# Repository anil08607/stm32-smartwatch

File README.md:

# Anil nRF52810 Smartwatch V1

A 46 × 46 mm, four-layer Bluetooth smartwatch PCB with a Nordic nRF52810-QFAA, 240 × 240 SPI LCD interface, BMA456 accelerometer, battery-backed PCF8563 RTC, USB-C 5 V charging, protected single-cell battery interface, bonded battery NTC, two buttons and haptic motor output. USB-C faces the left side, clear of both straps; two buttons form a centred pair on the right side.

**Release status: engineering review / prototype handoff. Production ordering is blocked until the explicit gates in `release/readiness.json` are closed.** Passing software checks does not establish RF performance, battery safety, assembly orientation or enclosure fit. No hardware test results or working smartwatch firmware are claimed.

## Open the design

- `index.circuit.tsx`: complete compact product assembly by default, with the actual routed PCB underneath.
- `pcb.circuit.tsx`: dedicated routed PCB/schematic view and PCB-only inspection.
- `assembly-exploded.circuit.tsx`: separated product stack for battery, display, buttons, wiring and enclosure inspection.
- `assembly.circuit.tsx`: routed PCB plus external product assembly in the tscircuit 3D viewer.
- `SMARTWATCH_V1_NRF52810.circuit.tsx`: editable electrical design, exact parts, placement and protected critical routes.
- `hardware/smartwatch-nrf52810.kicad_pro`: portable native KiCad 10 project, seven electrical sheets and local symbol/footprint libraries.
- `mechanical/index.html`: interactive compact/exploded assembly. Run `bun run preview:assembly`, then open http://127.0.0.1:8766/mechanical/.
- `mechanical/`: compact/exploded GLB, five printable STL parts and dimension/part manifest. The provisional case is 54 × 54 × 18 mm with 22 mm strap lugs. Bodies and harnesses are fit envelopes.
- `release/full-purchase-list.csv`: fitted SMT parts, LCD, battery, NTC, motor, harnesses, enclosure, lens, fastening, strap and tools, with purchase URLs.

## Reproduce the checks

Install Bun 1.3.14, then `bun install --frozen-lockfile`. Run `bun run verify` for formatting, type checks, a fresh editable-source build, strict saved-route binding, connectivity, routing, assembly, schematic-style checks, all four actual viewer entries and the hosted multi-file CLI build and a stale-geometry rejection test. `bun run check:native` runs the actual KiCad DRC and ERC (KiCad 10 required; set `KICAD_CLI` if it is not on PATH). `bun run check:stock` refreshes public exact-part JLCPCB inventory. `bun run check:order` is intentionally strict and fails while any qualification or purchasing gate is unresolved.

The hosted build uses `bun run build:site` and only the four public entrypoints. Its optional parts engine is off because footprints and exact MPNs are committed and audited separately; inventory is checked by `check:stock`. No DRC or warning-ignore flags are used. Connector pin-1 display annotations cannot invalidate routing; changes to pads, positions, nets or copper still do.

Source/geometry edits invalidate the routed artifact and release evidence. Follow `routing/README.md`; never bypass the fingerprint or regenerate only the screenshots. Manufacturing outputs come from the reviewed native board, not from an unrouted viewer export.

## Hardware boundaries

The nRF52810 has 192 KiB flash and 24 KiB RAM. A 240 × 240 RGB565 framebuffer needs 115,200 bytes; firmware must use line/tile rendering. This revision has BLE, a no-touch LCD, motion sensing, RTC, buttons and haptics. It does not include Wi-Fi, a touch controller or an optical heart-rate sensor.

The main rail is nominally 3.05 V (510 kΩ / 100 kΩ feedback). The MCU uses its internal LDO; DCC is unconnected and firmware must leave DCDCEN=0. RF matching values are reference starting values. The antenna keepout spans all copper layers; final fabricator stackup, impedance and enclosure tuning remain mandatory.

Only the 70 fitted top-side parts belong in the SMT BOM/CPL. M1 is a pair of motor wire pads with no paste; the motor is installed after reflow. J2 and J5 use identical connector families but carry battery power and NTC respectively: label harnesses and verify polarity before connection.

See [assembly](docs/assembly.md), [fabrication](docs/fabrication.md), [bring-up](docs/bring-up.md), [sourcing](sourcing/README.md), [firmware interface](firmware/README.md) and [manufacturer references](REFERENCES.md).

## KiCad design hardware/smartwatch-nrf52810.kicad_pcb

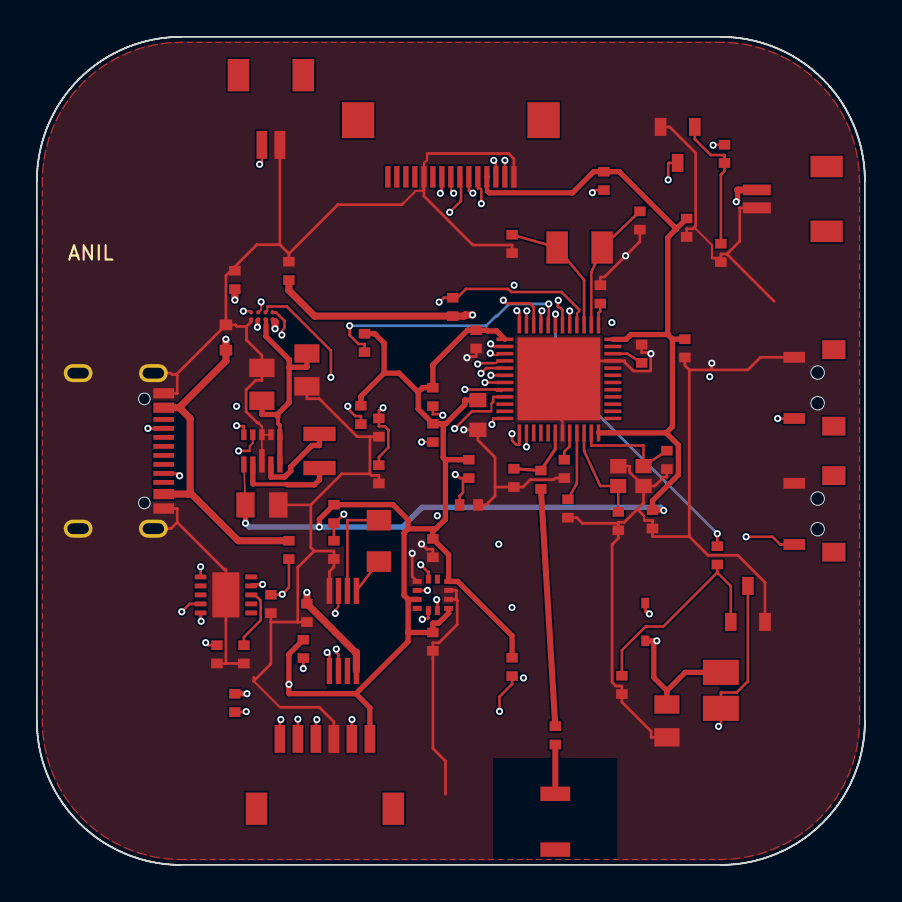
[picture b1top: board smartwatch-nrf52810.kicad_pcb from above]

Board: 4 copper layers, 46.0 x 46.0 mm, 71 parts (0 on the bottom side), 53 nets.

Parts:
ANT1: RFANT3216120A5T; ANT1_exact
C1: 1uF; C1_exact
C2: 10uF; C2_exact
C3: 1uF; C3_exact
C4: 10uF; C4_exact
C5: 22uF; C5_exact
C6: 1uF; C6_exact
C8: 100nF; C8_exact
C9: 100pF; C9_exact
C10: 100nF; C10_exact
C11: 1uF; C11_exact
C12: 4.7uF; C12_exact
C13: 100nF; C13_exact
C14: 100nF; C14_exact
C15: 100nF; C15_exact
C16: 100nF; C16_exact
C17: 100nF; C17_exact
C22: 100nF; C22_exact
C23: 22uF; C23_exact
C24: 0.8pF; C24_exact
C25: 100nF; C25_exact
C26: 100nF; C26_exact
C27: 100nF; C27_exact
C28: 12pF; C28_exact
C29: 12pF; C29_exact
C30: 12pF; C30_exact
C31: 12pF; C31_exact
D1: D; D1_exact
D2: D; D2_exact
J1: J1; J1_exact
J2: J2; J2_exact
J3: J3; J3_exact
J4: J4; J4_exact
J5: J5; J5_exact
L1: 470nH; L1_exact
L2: 3.9nH; L2_exact
L3: 6.8nH; L3_exact
M1: M1; M1_exact
Q1: Q1; Q1_exact
Q2: Q2; Q2_exact
R1: 0Ω; R1_exact
R2: 0Ω; R2_exact
R4: 510kΩ; R4_exact
R5: 100kΩ; R5_exact
R6: 100kΩ; R6_exact
R7: 10kΩ; R7_exact
R8: 4.7kΩ; R8_exact
R9: 4.7kΩ; R9_exact
R10: 10kΩ; R10_exact
R12: 1MΩ; R12_exact
R13: 330kΩ; R13_exact
R14: 22Ω; R14_exact
R15: 100Ω; R15_exact
R16: 100kΩ; R16_exact
R17: 10kΩ; R17_exact
R18: 10Ω; R18_exact
R19: 100kΩ; R19_exact
R20: 100kΩ; R20_exact
R21: 100Ω; R21_exact
R22: 100kΩ; R22_exact
SW1: SW1; SW1_exact
SW2: SW2; SW2_exact
U1: NRF52810-QFAA-R; U1_exact
U2: BMA456; U2_exact
U3: HUSB238_002DD; U3_exact
U4: PCF8563TS/5,118; U4_exact
U5: BQ25180YBGR; U5_exact
U6: TPS63802DLAR; U6_exact
Y1: Y1; Y1_exact
Y2: Y2; Y2_exact
Y3: Y3; Y3_exact

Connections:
BAT: C3.1, C22.1, J2.1, R12.1, U4.8, U5.6
BAT_ADC: C14.1, R12.2, R13.1, U1.4
BMA_INT1: U1.18, U2.5
BMA_INT2: U1.19, U2.6
BQ_TS: J5.1, U5.7
BUCK_FB: R4.2, R5.1, U6.4
BUCK_L1: L1.1, U6.9
BUCK_L2: L1.2, U6.7
BUCK_PG: R6.2, U6.5
BUTTON1: R19.2, SW1.1, U1.5
BUTTON2: R20.2, SW2.1, U1.6
CHG_INT: R7.2, U1.8, U5.1
DEBUG_GPIO: J3.6, U1.21
DISPLAY_LEDA: J4.3, R14.2
DISPLAY_LED_K: J4.2, Q1.3
GND: C1.2, C2.2, C3.2, C4.2, C5.2, C6.2, C8.2, C9.2, C10.2, C11.2, C12.2, C13.2, C14.2, C15.2, C16.2, C17.2, C22.2, C23.2, C24.2, C25.2, C26.2, C27.2, C28.2, C29.2, C30.2, C31.2, D1.1, J1.1, J1.12, J1.13, J1.14, J1.15, J1.16, J2.2, J3.3, J4.1, J4.11, J5.2, Q1.2, Q2.2, R1.2, R2.2, R5.2, R13.2, R16.2, R22.2, SW1.2, SW2.2, U1.31, U1.45, U1.49, U2.1, U2.8, U2.9, U3.11, U4.4, U5.8, U6.2, U6.3, U6.8, Y2.2, Y2.4
HF_X1: C28.1, U1.34, Y2.1
HF_X2: C29.1, U1.35, Y2.3
I2C_SCL: R8.2, U1.16, U2.12, U4.6, U5.3
I2C_SDA: R9.2, U1.17, U2.2, U4.5, U5.5
LCD_BL: R15.1, U1.15
LCD_BL_GATE: Q1.1, R15.2, R16.1
LCD_CS: J4.6, U1.9
LCD_DC: J4.5, U1.12
LCD_MOSI: J4.8, U1.11
LCD_RESET: J4.9, U1.14
LCD_SCK: J4.7, U1.10
LF_X1: C30.1, U1.2, Y3.1
LF_X2: C31.1, U1.3, Y3.2
MOTOR_EN: R21.1, U1.7
MOTOR_GATE: Q2.1, R21.2, R22.1
MOTOR_NEG: D2.1, M1.2, Q2.3
NRF_DEC1: C8.1, U1.1
NRF_DEC2: C9.1, U1.32
NRF_DEC3: C10.1, U1.33
NRF_DEC4: C11.1, U1.46
NRST: C13.1, J3.5, R10.2, U1.24
PD_ISET: R2.1, U3.9
PD_VIN: C6.1, R18.2, U3.1
PD_VSET: R1.1, U3.8
RF_50: L2.2, L3.1
RF_ANT: C24.1, L2.1, U1.30
RF_FEED: ANT1.1, L3.2
RTC_INT: R17.2, U1.20, U4.3
RTC_OSCI: U4.1, Y1.1
RTC_OSCO: U4.2, Y1.2
SWCLK: J3.4, U1.25
SWDIO: J3.2, U1.26
SYS: C2.1, C4.1, U5.4, U6.1, U6.10
USB5V: C1.1, D1.2, J1.2, J1.11, R18.1, U5.2
USB_CC1: J1.4, U3.4
USB_CC2: J1.9, U3.5
V3V0: C5.1, C12.1, C15.1, C16.1, C17.1, C23.1, C25.1, C26.1, C27.1, D2.2, J3.1, J4.4, M1.1, R4.1, R6.1, R7.1, R8.1, R9.1, R10.1, R14.1, R17.1, R19.1, R20.1, U1.13, U1.36, U1.48, U2.3, U2.7, U2.10, U6.6

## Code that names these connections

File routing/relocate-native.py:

"""Create the side-access routing seed from the previous reviewed board.

The source board path is explicit so a fresh design cannot silently reuse this migration.
Rotate the complete layout clockwise, then relocate the two switches, SWD header
and one pull-up. Rip up affected signal nets and copper inside the new lands.
"""
from pathlib import Path
import sys,json,shutil
import pcbnew as p,wx
wx.Log.SetLogLevel(0);app=wx.App(False)
b=p.LoadBoard(str(Path(sys.argv[1]).resolve()))
centre=p.VECTOR2I(p.FromMM(100),p.FromMM(100));angle=p.EDA_ANGLE(270,p.DEGREES_T)
for item in list(b.GetFootprints())+list(b.GetTracks())+list(b.Zones())+list(b.GetDrawings()):item.Rotate(centre,angle)
def point(x,y):return p.VECTOR2I(p.FromMM(100+x),p.FromMM(100-y))
positions={'SW1':(20.2,3.5,90),'SW2':(20.2,-3.5,90),'J3':(-7,-18,180),'R20':(-12,-14,270)}
rects=[]
for f in b.GetFootprints():
 if f.GetReference() not in positions:continue
 x,y,a=positions[f.GetReference()];f.SetPosition(point(x,y));f.SetOrientationDegrees(a)
 r=f.GetBoundingBox(False,False);r.Inflate(p.FromMM(.4));rects.append(r)
held=[];removed={}
for t in list(b.GetTracks()):
 if t.GetNetname() in {'BUTTON1','BUTTON2','SWCLK','SWDIO','NRST','DEBUG_GPIO'} or any(r.Intersects(t.GetBoundingBox()) for r in rects):
  removed[t.GetNetname()]=removed.get(t.GetNetname(),0)+1;b.Delete(t)
# Source placement positions and every physical land must agree before routing.
c=json.loads(Path('routing/source.circuit.json').read_text());names={x['source_component_id']:x['name'] for x in c if x['type']=='source_component'}
for f in b.GetFootprints():
 comp=next(x for x in c if x['type']=='pcb_component' and names[x['source_component_id']]==f.GetReference())
 assert abs(p.ToMM(f.GetPosition().x)-100-comp['center']['x'])<.0001,(f.GetReference(),'x')
 assert abs(100-p.ToMM(f.GetPosition().y)-comp['center']['y'])<.0001,(f.GetReference(),'y')
Path('build/native').mkdir(parents=True,exist_ok=True)
p.SaveBoard(str(Path('build/native/smartwatch-nrf52810.kicad_pcb').resolve()),b)
shutil.copyfile(Path(sys.argv[1]).with_suffix('.kicad_pro'),'build/native/smartwatch-nrf52810.kicad_pro')
print('Relocated native seed; removed copper by net:',json.dumps(removed,sort_keys=True))
